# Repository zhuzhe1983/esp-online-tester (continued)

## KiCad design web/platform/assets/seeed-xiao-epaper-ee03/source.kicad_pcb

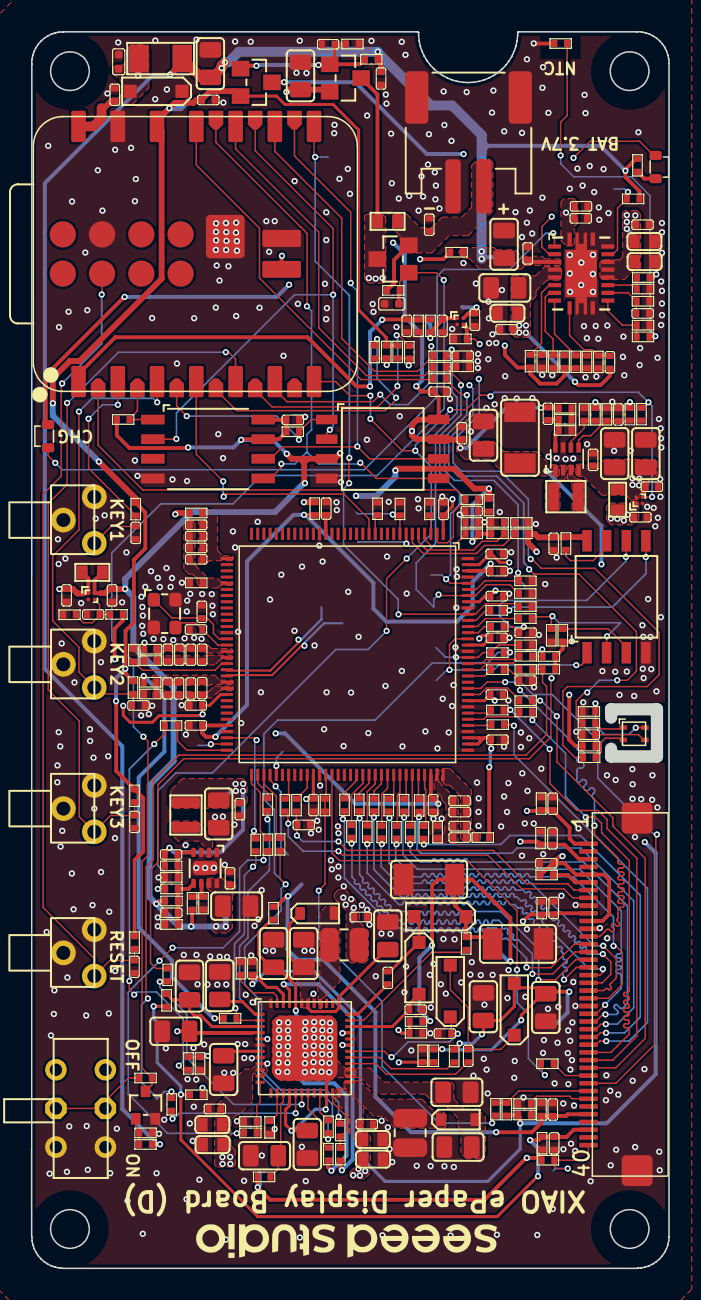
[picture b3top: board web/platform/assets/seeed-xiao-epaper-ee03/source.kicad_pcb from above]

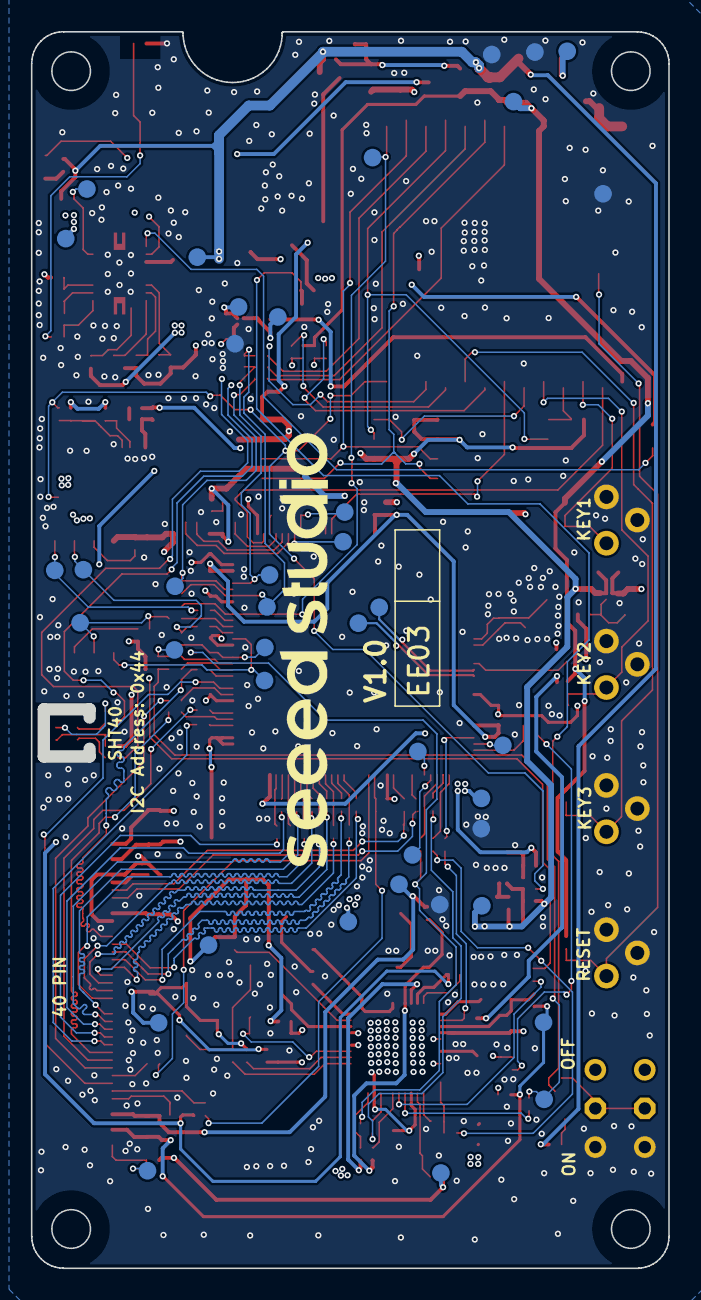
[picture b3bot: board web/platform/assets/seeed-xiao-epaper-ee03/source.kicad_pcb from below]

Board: 4 copper layers, 41.2 x 80.0 mm, 357 parts (40 on the bottom side), 201 nets.

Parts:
C1: 4.7uF; C0402
C2, C10, C13, C17, C18, C19, C84, C117: 10uF; C0402
C3, C11, C15, C20, C39, C41, C42, C48, C52, C64, C72, C73: 1uF; C0402
C4, C35, C71: 22uF; C0805
C5, C6, C7, C8, C62: 1nF; C0402
C9, C24, C28, C69, C75, C77: 10uF; C0805
C12, C16, C22, C130: 100pF; C0402
C14, C23: 4.7uF; C1206
C21, C78, C141: 10nF; C0402
C25, C27, C29, C31, C34, C36, C38, C43, C49, C50, C53, C54, C55, C56, C58, C59, C61, C63, C70, C74, C76, C85, C90, C91, C98, C103, C104, C112, C113, C115, C116, C120, C121, C124, C125, C126, C127, C128, C129, C132, C139, C142, C144, C145, C148, C190: 100nF; C0402
C26: 47uF; C1206
C30: 470nF; C0402
C37, C40, C57: 10uF; C0603
C67: 220nF; C0402
C81, C100, C114, C122: 22uF; C0603
C105, C108: 12pF; C0402
C118, C131: 18pF; C0402
C119, C123, C133, C134, C135, C136, C137, C138, C140, C143, C146, C147, C149: 4.7uF; C0805
D1, D3, D4, D6: MMSD4148; SOD-123
D2, D10: B5819WS SL; SOD-323
D5, D16: Green; LED2-0.6X1.7MM
D7: SMF5.0CA; SOD-123
D8, D9: TPD1E10B06DPYR; ESD-0402
F1: 2A; F1206
J1: AFC24-S40FIA-00; FPC40_0D5_23_5X4_9X2MM
J3: A2001WF-02A; JST2+2P_2.0_PH_S2B-PH-SM4-TB_1x02-1MP_Horizontal
L3: 2.2uH; L2520
L5: 4.7uH; L2520
L6, L7: 1uH; L2016
Q3, Q5, Q7: CJ3407; SOT23
Q4: LBSS138WT1G; SOT-323
R1, R3, R4, R5: 47K; R0402
R2: 100R; R0402
R7, R9, R10, R12, R17, R21, R26, R45, R46, R47, R48, R49, R52, R57, R59, R60, R61, R64, R65, R66, R67, R68, R70, R72, R73, R74, R75, R76, R85, R86, R87, R88, R89, R90, R91, R92, R93, R94, R95, R96, R97, R98, R99, R102, R103, R104, R105, R107, R108, R109, R110, R111, R113, R114, R116, R121, R122, R123, R126, R128, R130, R131, R132, R133, R150, R152, R153, R154, R155, R156, R157, R158, R159: 0R; R0402
R8: 22R; R0402
R11, R18, R19, R23: 4.7K; R0402
R13, R14, R32: 0R; R0603
R15, R24, R25, R27, R34, R40, R43, R44, R50, R51, R53, R54, R55, R56, R63, R69, R78, R80, R81, R82, R83, R136, R137, R138, R139, R141: 100K; R0402
R16, R22: 1K; R0402
R20: NCP15XH103F03RC; R0402
R28, R29, R30, R31, R35, R36, R37, R38, R39, R41, R71, R77, R100, R101, R106, R115, R124, R125, R127, R142, R143, R144, R145, R146, R147, R148, R149, R249, R255: 10K; R0402
R33: 80.6K; R0402
R42: 3.57K; R0402
R58: 12K; R0402
R62, R117, R119, R129: 1M; R0402
R79: 49.9R; R0402
R84: 36K; R0402
R112: 43K; R0402
R118: 52.3K; R0402
R120: 36.5K; R0402
R134: 511K; R0402
R135: 91K; R0402
R140: 200K; R0402
SW1: MK-22D18 G3; SW6-2CH-2.54-9X3.5X3.5
SW2, SW3, SW4, SW5: EL-4501V; SW3-DIP-SIDE-4.5X4.5X5.5MM
TP3, TP4, TP7, TP8, TP10, TP11, TP12, TP13, TP15, TP16, TP17, TP18, TP19, TP20, TP21, TP22, TP23, TP24, TP25, TP26, TP27, TP31, TP32, TP37, TP38, TP39, TP40, TP41, TP42, TP43, TP44, TP45, TP46, TP48, TP54, TP55, TP56, TP57, TP58, TP59: Test Point; TP-D45MIL
U1: BQ24070RHLR; RHL20_2P05X3P05
U3: XIAO-HALF-HOLE-33P; XIAO-ESP32-S3-Plus-SMD
U5, U7: ZB25VQ32DSJG; SOIC8-1.27-5.3X5.3MM
U6: GT30L32S4W; SOP8-1.27-5.2X5.2x2.16MM
U8: SHT40-AD1B-R2; SMD4-1.5X1.5X0.54MM
U10: TPS651851RSLR; VQFN48-0.4-6X6X1MM
U12: IT8951E/DX; LQFP128-0.4-14X14X1.6MM
U13: TPS631000DRLR; SOT-583
U14: ETA3410D2I-T; DFN8G-0.5-2X2MM
U17, U18, U19: TPS22916CYFPR; WLCSP4-0.4-0.77X0.77X0.33MM
X2: 12MHz 12pF; X4-SMD-2.5X2.0MM

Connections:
/E-ink/BORDER: J1.40, R60.2, TP31.1 (T)
/E-ink/PWRGOOD: R41.1, R132.2, U10.23 (PWR_GOOD)
/E-ink/PWRUP: R110.2, U10.21 (PWRUP)
/E-ink/S_XOE: J1.33, R126.2, R127.1
/E-ink/S_XSTL: J1.31, R59.2
/E-ink/TEST: J1.34, R121.2, R122.1
/E-ink/VB_OUT: C137.2, C143.2, D10.2, U10.37 (VDDH_IN), U10.42 (VB), U10.43 (VPOS_IN)
/E-ink/VB_SW: D10.1, L3.1, U10.40 (VB_SW)
/E-ink/VCOM_CTRL: R108.2, R129.1, U10.12 (VCOM_CTRL)
/E-ink/VDDH_FB: R119.2, R120.2, U10.33 (VDDH_FB)
/E-ink/VEE_FB: R117.2, R118.1, U10.31 (VEE_FB)
/E-ink/VNEG_OUT: C123.1, R104.2, U10.3 (VNEG)
/E-ink/VN_OUT: C133.1, C134.1, C138.2, C140.2, D2.1, U10.4 (VNEG_IN), U10.16 (VCOM_PWR), U10.22 (PBKG), U10.26 (VN), U10.27 (VEE_IN), U10.49 (EPAD)
/E-ink/VPOS_OUT: C147.1, R109.1, R116.1, U10.44 (VPOS)
/E-ink/WAKEUP: R63.2, R105.2, U10.5 (WAKEUP)
/TCON-IT8951/ALERT: R57.1, R124.2, TP48.1 (T), U12.112 (PWR_ALERT)
/TCON-IT8951/CFG0: R50.2, R51.1, U12.4 (TEST_CFG0)
/TCON-IT8951/CFG1: R53.2, R54.1, U12.5 (TEST_CFG1)
/TCON-IT8951/CFG2: R55.2, R56.1, U12.6 (TEST_CFG2)
/TCON-IT8951/HOLD#: R101.1, U7.7 (/HOLD(IO3))
/TCON-IT8951/ITE_HOST_HD_C: R255.1, U12.12 (HOST_HD_C)
/TCON-IT8951/ITE_RX: R77.1, TP54.1 (T), U12.8 (UART_RX)
/TCON-IT8951/ITE_TX: TP56.1 (T), U12.7 (UART_TX)
/TCON-IT8951/SDDO0_OUT: R87.1, U12.82 (SDDO0)
/TCON-IT8951/SDDO1_OUT: R86.1, U12.83 (SDDO1)
/TCON-IT8951/SDDO2_OUT: R85.1, U12.84 (SDDO2)
/TCON-IT8951/SDDO3_OUT: R68.1, U12.85 (SDDO3)
/TCON-IT8951/SDDO4_OUT: R67.1, U12.86 (SDDO4)
/TCON-IT8951/SDDO5_OUT: R66.1, U12.87 (SDDO5)
/TCON-IT8951/SDDO6_OUT: R65.1, U12.88 (SDDO6)
/TCON-IT8951/SDDO7_OUT: R64.1, U12.89 (SDDO7)
/TCON-IT8951/SDDO8_OUT: R61.1, U12.90 (SDDO8/GPIO0)
/TCON-IT8951/SDDO9_OUT: R52.1, U12.91 (SDDO9/GPIO1)
/TCON-IT8951/SDDO10_OUT: R49.1, U12.92 (SDDO10/GPIO2)
/TCON-IT8951/SDDO11_OUT: R48.1, U12.93 (SDDO11/GPIO3)
/TCON-IT8951/SDDO12_OUT: R90.1, U12.101 (SDDO12/GPIO4)
/TCON-IT8951/SDDO13_OUT: R89.1, U12.102 (SDDO13/GPIO5)
/TCON-IT8951/SDDO14_OUT: R88.1, U12.103 (SDDO14/GPIO6)
/TCON-IT8951/SDDO15_OUT: R114.1, U12.106 (SDDO15/GPIO7)
/TCON-IT8951/SPI_CS: TP37.1 (T), U7.1 (/CS), U12.115 (SPI_CS#)
/TCON-IT8951/SPI_SCK: C7.2, R95.2, TP40.1 (T), U7.6 (CLK)
/TCON-IT8951/SPI_SI: R94.2, R115.1, TP38.1 (T), U7.2 (DO(IO1))
/TCON-IT8951/SPI_SO: R93.2, TP39.1 (T), U7.5 (DI(IO0))
/TCON-IT8951/TEST_EN: R71.1, U12.3 (TEST_EN)
/TCON-IT8951/USB_N: TP19.1 (T), U12.51 (DM)
/TCON-IT8951/USB_P: TP25.1 (T), U12.52 (DP)
/TCON-IT8951/WP#: R100.1, U7.3 (/WP(IO2))
/TCON-IT8951/XSCI: C118.2, U12.46 (XSCI), X2.1
/TCON-IT8951/XSCO: C131.2, U12.47 (XSCO), X2.3
/XIAO/BUTON1: C54.1, R36.1, SW3.2, U3.2 (GPIO2_D1/A1)
/XIAO/BUTON2: C55.1, R37.1, SW4.2, U3.3 (GPIO3_D2/A2)
/XIAO/BUTON3: C56.1, R38.1, SW5.2, U3.5 (GPIO5_D4/A4/I2C_SDA)
/XIAO/IO41/I2C_SCL: R11.1, R17.1, R155.2
/XIAO/IO42/I2C_SDA: R12.1, R23.1, R154.2
/XIAO/PWR_SW: C41.1, Q5.1 (G), Q7.1 (G), R43.2, R145.1
/XIAO/RST: C53.1, R35.1, SW2.2, U3.26 (EN)
/XIAO/SPI1_CLK: U3.21 (GPIO11_DVP_Y8/SPI_MOSI1), U5.6 (CLK), U6.6 (CLK)
/XIAO/SPI1_CS0: R39.1, U3.16 (GPIO39_CAM_SCL/I2S_SCK), U6.1 (/CS)
/XIAO/SPI1_CS1: R31.1, U3.17 (GPIO40_CAM_SDA/I2S_WS), U5.1 (/CS)
/XIAO/SPI1_MISO: U3.22 (GPIO12_DVP_Y7/SPI_MISO1), U5.2 (DO(IO1)), U6.2 (DO(IO1))
/XIAO/SPI1_MOSI: U3.23 (GPIO13_DVP_PCLK/SPI_SCK1), U5.5 (DI(IO0)), U6.5 (DI(IO0))
ADC_EN: R27.2, U3.6 (GPIO6_D5/A5/I2C_SCL), U17.B2 (EN)
BAT_ADC: C62.1, R28.1, R29.2, U3.1 (GPIO1_D0/A0)
EDP_BUSY: U3.4 (GPIO4_D3/A3), U12.13 (HOST_HRDY)
EDP_Drive: C18.1, C64.1, C81.2, C84.1, C100.2, C114.2, C117.1, C122.2, L3.2, R13.2, TP22.1 (T), U10.10 (VIN), U10.24 (VIN_P), U18.A1 (VOUT)
EDP_RES: R2.2, U3.15 (GPIO38_DVP_VSYNC/I2S_SD), U12.2 (RESET#)
EPD_3V3: C19.1, C139.1, J1.5, J1.11, R121.1, R127.2, R249.2, U10.46 (V3P3)
ESP_3V3: C59.1, Q7.2 (S), R11.2, R23.2, R35.2, R36.2, R37.2, R38.2, TP10.1 (T), U3.12 (VCC_3V3)
GDCLK: C6.2, J1.7, R91.2
GDSPV: J1.8, R92.2
GND: C1.1, C4.2, C5.1, C6.1, C7.1, C8.1, C9.2, C14.2, C18.2, C19.2, C23.2, C24.1, C25.2, C26.2, C27.1, C28.2, C29.2, C30.1, C31.1, C34.2, C35.2, C36.2, C37.2, C38.2, C39.2, C40.2, C41.2, C42.2, C43.1, C48.2, C49.2, C50.2, C52.2, C53.2, C54.2, C55.2, C56.2, C57.2, C58.2, C59.2, C61.2, C62.2, C63.2, C64.2, C69.2, C70.2, C71.2, C72.2, C73.2, C74.2, C75.2, C76.2, C77.2, C78.2, C81.1, C84.2, C85.2, C90.2, C91.2, C98.2, C100.1, C103.2, C104.2, C112.2, C113.2, C114.1, C115.2, C116.2, C117.2, C118.1, C119.2, C120.2, C121.2, C122.1, C123.2, C124.2, C125.2, C128.2, C129.2, C131.1, C132.2, C133.2, C134.2, C135.2, C136.2, C137.1, C138.1, C139.2, C140.1, C143.1, C144.2, C145.2, C146.1, C147.2, C149.1, C190.2, D7.2, D8.1, D9.1, J1.9, J1.12, J1.22, J1.41, J1.42, J3.2, J3.3, J3.4, L5.2, Q4.2 (S), R1.1, R3.1, R4.1, R5.1, R15.1, R20.1, R26.1, R27.1, R29.1, R33.1, R34.1, R40.1, R42.1, R43.1, R44.1, R51.2, R54.2, R56.2, R58.1, R63.1, R71.2, R74.1, R76.1, R77.2, R78.1, R80.2, R81.2, R82.2, R83.2, R84.1, R98.1, R102.1, R111.1, R112.2, R115.2, R118.2, R120.1, R122.2, R124.1, R129.2, R135.2, R136.2, R138.1, R141.1, R142.1, R144.1, R147.1, R153.1, R255.2, SW1.CH1B, SW1.CH2B, SW2.1, SW2.3 (GND), SW3.1, SW3.3 (GND), SW4.1, SW4.3 (GND), SW5.1, SW5.3 (GND), TP4.1 (T), TP8.1 (T), TP13.1 (T), TP16.1 (T), TP17.1 (T), TP41.1 (T), U1.11 (VSS), U1.19 (GND), U1.20 (GND), U1.21 (EPAD), U3.13 (GND), U3.27 (GND1), U3.33 (GND2), U3.34 (PAD), U5.4 (GND), U6.4 (GND), U7.4 (GND), U10.6 (DGND), U10.8 (AGND1), U10.32 (PGND2), U10.41 (PGND1), U10.48 (AGND2), U12.21 (VSS), U12.45 (VS33D), U12.61 (VSS), U12.76 (VSS), U12.97 (VSS), U12.100 (VSS), U12.104 (VSS), U12.113 (VSS), U12.120 (VSS), U12.125 (VSS), U12.128 (VSS), U13.7 (GND), U14.1 (PGND), U14.3 (AGND), U14.9 (PAD), U17.B1 (GND), U18.B1 (GND), U19.B1 (GND), X2.2, X2.4
GND18A: C2.2, C3.2, C127.2, C130.1, R76.2, U12.95 (GND18A)
GND33A_HSRT: C13.2, C15.2, C16.1, C142.2, R98.2, U12.49 (GND33A__HSRT)
GND33A_U20: C17.2, C20.2, C22.1, C148.2, R102.2, U12.54 (GND33A_U20)
GNDAT: C10.2, C11.2, C12.1, C126.2, R74.2, U12.37 (GNDA)
ITE_I2C_SCL: R19.1, R46.2, R156.1, TP42.1 (T)
ITE_I2C_SDA: R18.1, R45.2, R157.1, TP43.1 (T)
unnamed: C1.2, R2.1, R125.1
unnamed: C21.2, D1.2, D6.1
unnamed: C141.2, D3.2, D4.1
unnamed: D5.1 (+), R148.1
unnamed: D5.2 (-), U1.3 (STAT2)
unnamed: D16.1 (+), R149.1
unnamed: D16.2 (-), U1.2 (STAT1)
unnamed: J1.6, R249.1
unnamed: D9.2, Q3.1 (G), Q4.3 (D), R8.2, R62.2
unnamed: C39.1, J3.1, Q3.2 (S), R32.2, R62.1
unnamed: Q4.1 (G), R16.2, R40.2
unnamed: C69.1, Q5.2 (S), U3.32 (VBAT)
unnamed: R8.1, SW1.COM1, SW1.COM2
unnamed: R20.2, R21.1
unnamed: R79.1, R134.2
unnamed: C58.1, D7.1, D8.2, F1.1, TP7.1 (T), U3.14 (VBUS)
unnamed: TP11.1 (T), U12.69 (GPIO15/PWR7)
unnamed: TP12.1 (T), U12.68 (GPIO14/PWR6)
unnamed: C49.1, R28.2, TP15.1 (T), U17.A1 (VOUT)
unnamed: R30.1, TP18.1 (T), U1.18 (~PG)
unnamed: TP57.1 (T), U12.63 (GPIO9/PWR1)
unnamed: R146.2, R147.2, U1.9 (CE)
unnamed: C78.1, R84.2, U1.13 (DPPM)
unnamed: C67.2, R42.2, U1.10 (ISET1)
unnamed: R139.1, R142.2, U1.7 (ISET2)
unnamed: R143.2, R144.2, U1.8 (MODE)
unnamed: R22.2, R33.2, U1.14 (TMR)
unnamed: R21.2, R26.2, U1.12 (TS)
unnamed: R10.1, U3.9 (GPIO7_D8/A8/SCK)
unnamed: R9.1, U3.10 (GPIO8_D9/A9/MISO)
unnamed: R7.1, U3.11 (GPIO9_D10/A10/MOSI)
unnamed: R17.2, U3.18 (GPIO41_PDM_DATA/RX1)
unnamed: R12.2, U3.19 (GPIO42_PDM_CLK/TX1)
unnamed: R155.1, U8.2 (SCL)
unnamed: R154.1, U8.1 (SDA)
unnamed: C85.1, R152.2, U8.3 (VDD)
unnamed: R153.2, U8.4 (VSS)
unnamed: C136.1, U10.7 (INT_LDO)
unnamed: R156.2, U10.17 (SCL)
unnamed: R157.2, U10.18 (SDA)
unnamed: R112.1, U10.47 (TS)
unnamed: C119.1, R103.2, U10.15 (VCOM)
unnamed: R111.2, U10.14 (VCOM_DIS)
unnamed: C144.1, D3.1, U10.34 (VDDH_D)
unnamed: R113.1, U10.35 (VDDH_DIS)
unnamed: C141.1, U10.36 (VDDH_DRV)
unnamed: C145.1, D6.2, U10.30 (VEE_D)
unnamed: R130.2, U10.29 (VEE_DIS)
unnamed: C21.1, U10.28 (VEE_DRV)
unnamed: R107.2, U10.9 (VNEG_DIS)
unnamed: D2.2, L5.1, U10.25 (VN_SW)
unnamed: R109.2, U10.19 (VPOS_DIS)
unnamed: C135.1, U10.1 (VREF)
unnamed: R91.1, U12.74 (GDCLK)
unnamed: R92.1, U12.71 (GDSPV)
unnamed: R131.2, U12.62 (GPIO8/PWR0)
unnamed: R133.2, U12.64 (GPIO10/PWR2)
unnamed: R96.1, U12.65 (GPIO11/PWR3)
unnamed: R123.1, U12.66 (GPIO12/PWR4)
unnamed: R150.1, U12.67 (GPIO13/PWR5)
unnamed: R46.1, U12.110 (I2C_SCL)
unnamed: R45.1, U12.111 (I2C_SDA)
unnamed: R58.2, U12.50 (RREF)
unnamed: R47.1, U12.109 (SDCLK)
unnamed: R93.1, U12.118 (SPI_MISO)
unnamed: R94.1, U12.117 (SPI_MOSI)
unnamed: R95.1, U12.116 (SPI_SCK)
unnamed: C43.2, R15.2, R24.1, R158.2, U13.5 (EN)
unnamed: C105.2, R134.1, R135.1, U13.8 (FB)
unnamed: L6.1, U13.3 (LX1)
unnamed: L6.2, U13.2 (LX2)
unnamed: R69.1, R78.2, U13.6 (MODE)
unnamed: C27.2, R25.1, R136.1, R159.1, U14.5 (EN)
unnamed: C108.2, R140.1, R141.2, U14.4 (FB)
unnamed: R137.1, R138.2, U14.6 (MODE)
unnamed: L7.1, U14.2 (SW)
unnamed: C38.1, R34.2, R70.1, U19.B2 (EN)
PWR0_INT: R106.1, R131.1, U10.2 (NINT)
PWR2_WAKEUP: R105.1, R133.1
PWR3_PWRCOM: R96.2, R108.1
PWR4_PWRUP: R110.1, R123.2
PWR5_GOOD: R57.2, R132.1, R150.2
PWR_EN: R158.1, R159.2, U3.7 (U0TXD_D6/TX), U18.B2 (EN)
SDCE_N0: R59.1, U12.78 (SDCE_N0)
SDCLK: C5.2, J1.13, R47.2
SDDO0: J1.14, R87.2
SDDO1: J1.15, R86.2
SDDO2: J1.16, R85.2
SDDO3: J1.17, R68.2
SDDO4: J1.18, R67.2
SDDO5: J1.19, R66.2
SDDO6: J1.20, R65.2
SDDO7: J1.21, R64.2
SDDO8: J1.23, R61.2
SDDO9: J1.24, R52.2
SDDO10: J1.25, R49.2
SDDO11: J1.26, R48.2
SDDO12: J1.27, R90.2
SDDO13: J1.28, R89.2
SDDO14: J1.29, R88.2
SDDO15: J1.30, R114.2
SDLE: J1.32, U12.107 (SDLE)
SDOE: R126.1, R128.1, R128.2, U12.77 (SDOE)
SPI0_CLK: C8.2, R10.2, R81.1, TP44.1 (T), U12.122 (SPI2_SCK/I2C2_SCL)
SPI0_CS: R80.1, TP45.1 (T), U3.8 (U0RXD_D7/RX), U12.119 (SPI2_CS#/I2C_SDA)
SPI0_MISO: R9.2, R83.1, TP58.1 (T), U12.124 (SPI2_MISO/UART_RTS#)
SPI0_MOSI: R7.2, R82.1, TP59.1 (T), U12.123 (SPI2_MOSI/UART_CTS#)
TYPEC_5V: C24.2, C42.1, C71.1, C74.1, F1.2, R16.1, R30.2, R139.2, R143.1, R145.2, R146.1, R148.2, R149.2, TP26.1 (T), U1.4 (IN)
VBAT: C35.1, C36.1, C37.1, C48.1, C67.1, Q3.3 (D), Q5.3 (D), R32.1, TP3.1 (T), U1.5 (BAT), U1.6 (BAT), U17.A2 (VIN)
VCC3IO: C116.1, C121.1, C125.1, C129.1, R72.2, U12.20 (VCC3IO), U12.60 (VCC3IO), U12.94 (VCC3IO), U12.126 (VCC3IO)
VCC18A: C2.1, C3.1, C127.1, C130.2, R75.2, U12.96 (VCC18A)
VCC33A: C10.1, C11.1, C12.2, C126.1, R73.2, U12.33 (VCC33A)
VCC33A_HSRT: C13.1, C15.1, C16.2, C142.1, R97.2, U12.48 (VCC33A_HSRT)
VCC33A_U20: C17.1, C20.1, C22.2, C148.1, R99.2, U12.53 (VCC33A_U20)
VCC_3V3: C26.1, C28.1, C29.1, C50.1, C63.1, C72.1, C75.1, C76.1, C105.1, Q7.3 (D), R14.1, R25.2, R31.2, R39.2, R79.2, R137.2, R152.1, TP55.1 (T), U5.3 (/WP(IO2)), U5.7 (/HOLD(IO3)), U5.8 (VCC), U6.7 (/HOLD(IO3)), U6.8 (VCC), U13.1 (VOUT), U14.7 (AVIN), U14.8 (PVIN), U19.A2 (VIN)
VCC_ITE_3V3: C70.1, C73.1, R14.2, R18.2, R19.2, R41.2, R50.1, R53.1, R55.1, R72.1, R73.1, R97.1, R99.1, R100.2, R101.2, R106.2, R125.2, U7.8 (VCC), U10.45 (VIN3P3), U19.A1 (VOUT)
VCOM_OUT: C98.1, J1.10, R44.2, R60.1, R103.1, TP32.1 (T)
VDNG: C90.1, C146.2, C149.2, D1.1, J1.1, R5.2, R117.1, R130.1, TP23.1 (T)
VDNS_OUT: C103.1, J1.38, R3.2, R104.1, R107.1, TP20.1 (T)
VDPG: C14.1, C23.1, C91.1, D4.2, J1.3, R1.2, R113.2, R119.1, TP24.1 (T)
VDPS_OUT: C104.1, J1.36, R4.2, R116.2, TP21.1 (T)
VD_1V8: C34.1, C77.1, C108.1, C112.1, C113.1, C115.1, C120.1, C124.1, C128.1, C132.1, C190.1, L7.2, R70.2, R75.1, R140.2, TP46.1 (T), U12.1 (VCCK), U12.55 (VCCK), U12.75 (VCCK), U12.98 (VCC_SDRIO), U12.99 (VCCK), U12.105 (VCC_SDRIO), U12.114 (VCC_SDRIO), U12.121 (VCC_SDRIO), U12.127 (VCC_SDRIO)
VREF: C30.2, C31.2, R22.1, U1.1 (VREF)
VSYS: C4.1, C9.1, C25.1, C40.1, C52.1, C57.1, C61.1, R13.1, R24.2, R69.2, TP27.1 (T), U1.15 (OUT), U1.16 (OUT), U1.17 (OUT), U13.4 (VN), U18.A2 (VIN)
